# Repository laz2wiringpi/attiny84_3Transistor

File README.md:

# attiny84_3Transistor
attiny84 3 transistor

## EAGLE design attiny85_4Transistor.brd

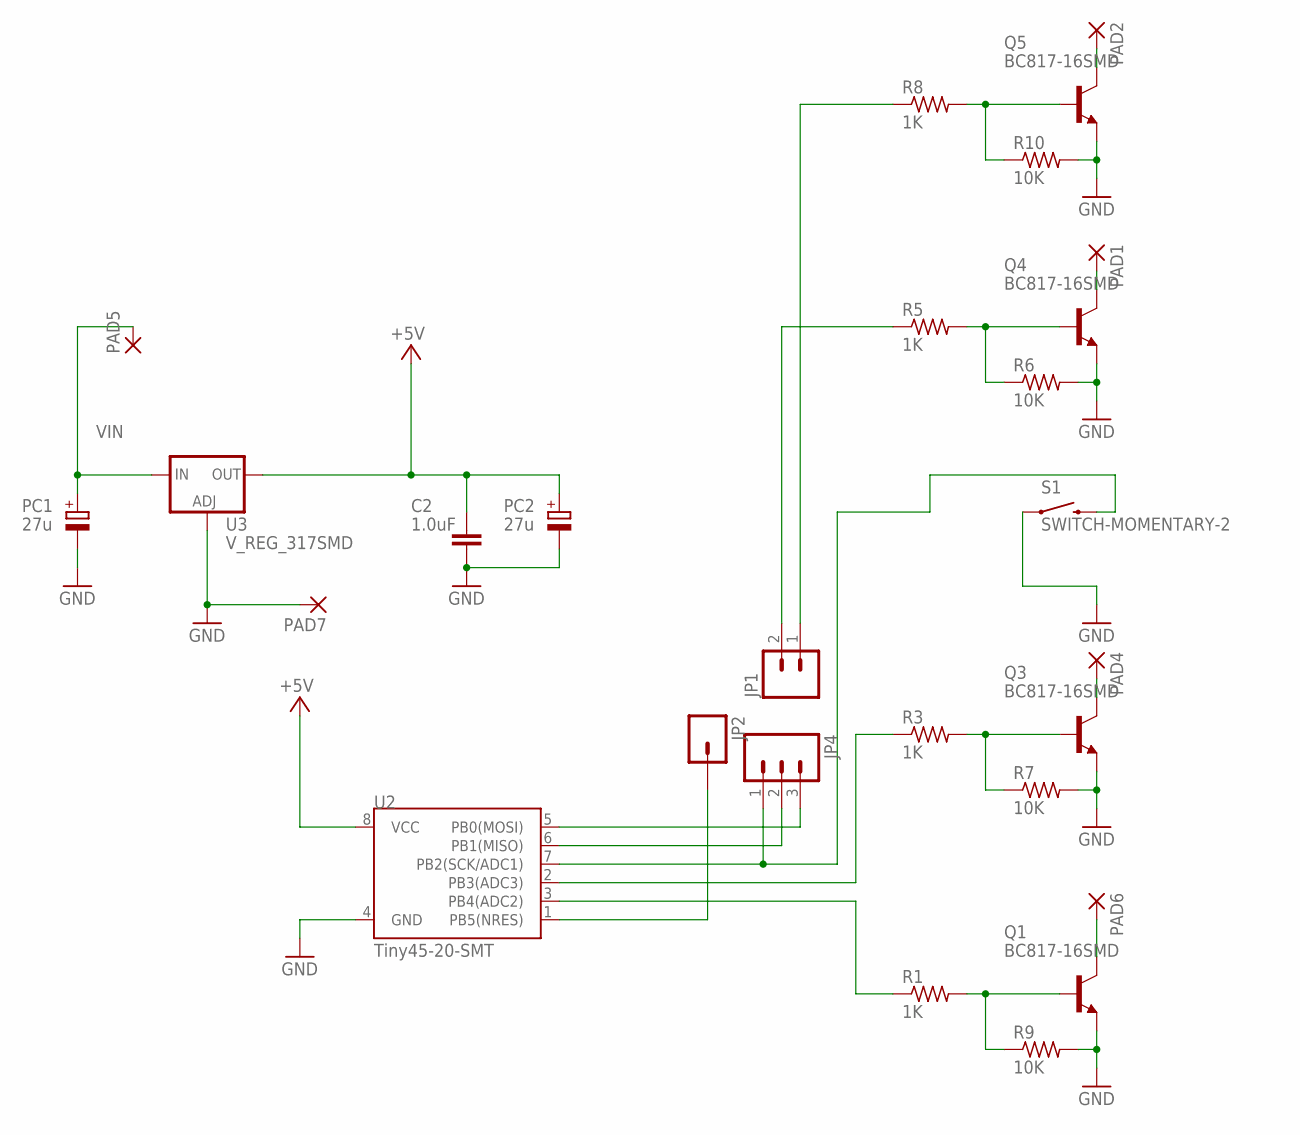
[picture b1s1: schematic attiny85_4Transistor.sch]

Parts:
C2: 1.0uF; 0805
JP1: M021X02_NO_SILK; 1X02_NO_SILK
JP2: M01PTH; 1X01
JP4: M031X03_NO_SILK; 1X03_NO_SILK
PAD1, PAD2, PAD4, PAD5, PAD6, PAD7: 2,15/1,0
PC1, PC2: 27u; E2,5-4R
Q1, Q3, Q4, Q5: BC817-16SMD; SOT23-BEC
R1, R3, R5, R8: 1K; R0805
R6, R7, R9, R10: 10K; M0805
S1: SWITCH-MOMENTARY-2; TACTILE_FSM4JSMATR
U2: Tiny45-20-SMT; SO08-EIAJ
U3: V_REG_317SMD; SOT223

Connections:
+5V: C2.2, PC2.+, U2.8 (VCC), U3.2 (OUT)
GND: C2.1, PAD7.1, PC1.-, PC2.-, Q1.E, Q3.E, Q4.E, Q5.E, R6.2, R7.2, R9.2, R10.2, S1.P$1 (1), S1.P$2 (1), U2.4 (GND), U3.1 (ADJ)
unnamed: Q4.B, R5.2, R6.1
unnamed: JP4.1, S1.P$3 (2), S1.P$4 (2), U2.7 (PB2(SCK/ADC1))
unnamed: Q1.B, R1.2, R9.1
unnamed: Q3.B, R3.2, R7.1
unnamed: PAD1.1, Q4.C
unnamed: PAD6.1, Q1.C
unnamed: JP2.1, U2.1 (PB5(NRES))
unnamed: PAD4.1, Q3.C
unnamed: Q5.B, R8.2, R10.1
unnamed: PAD2.1, Q5.C
PWM2: R3.1, U2.2 (PB3(ADC3))
PWM3: R1.1, U2.3 (PB4(ADC2))
PWM5J: JP1.1, R8.1
PWM5MOSI: JP4.3, U2.5 (PB0(MOSI))
PWM6J: JP1.2, R5.1
PWM6MISO: JP4.2, U2.6 (PB1(MISO))
VIN: PAD5.1, PC1.+, U3.3 (IN)

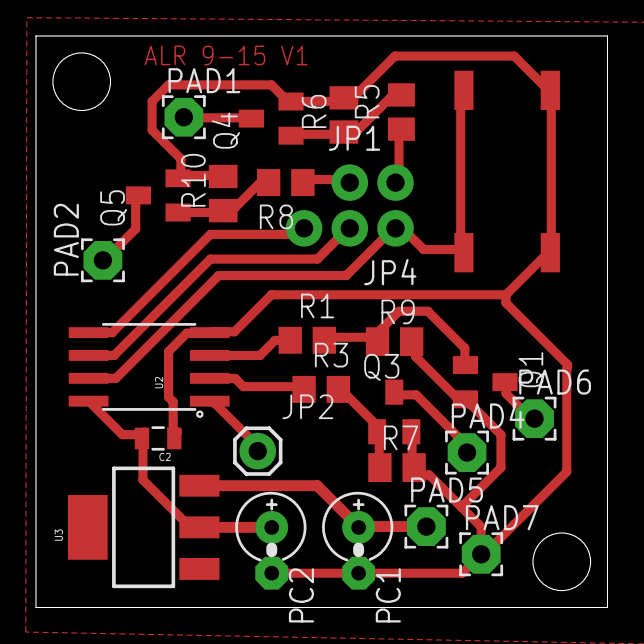
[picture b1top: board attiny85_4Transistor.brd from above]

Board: 2 copper layers, 31.8 x 31.8 mm, 27 parts (0 on the bottom side), 19 nets.

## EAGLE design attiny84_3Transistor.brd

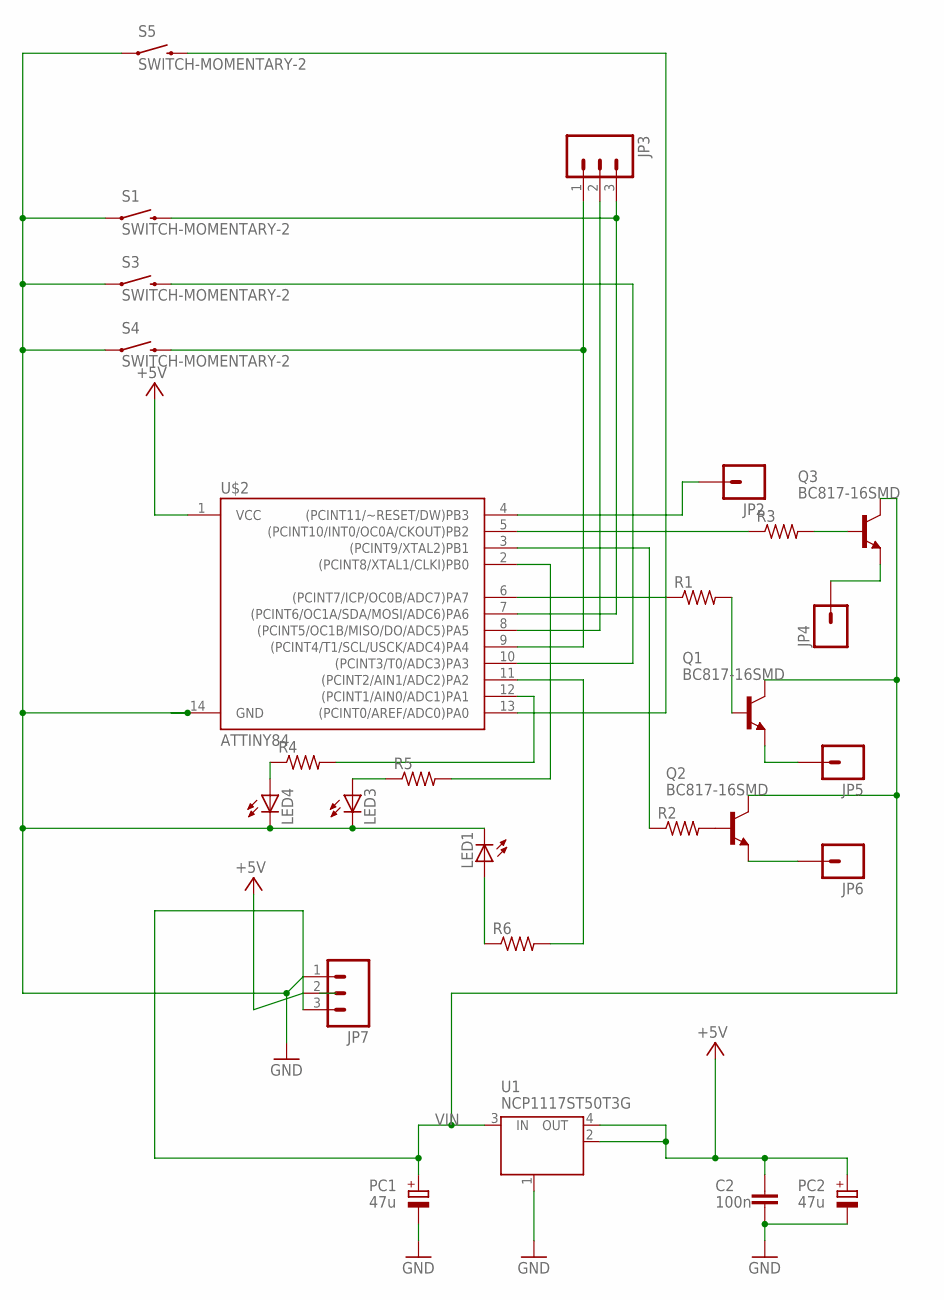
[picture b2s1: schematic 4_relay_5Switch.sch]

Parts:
C2: 100n; C0603-ROUND
JP2, JP4, JP5, JP6: M01NOSILK-KIT; 1X01NS-KIT
JP3, JP7: M031X03_NO_SILK; 1X03_NO_SILK
LED1, LED3, LED4: LEDCHIPLED_0805; CHIPLED_0805
PC1, PC2: 47u; E2,5-4R
Q1, Q2, Q3: BC817-16SMD; SOT23-BEC
R1, R2, R3, R4, R5, R6: R-US_M0805; M0805
S1, S3, S4, S5: SWITCH-MOMENTARY-2; TACTILE_FSM4JSMATR
U1: NCP1117ST50T3G; SOT223
U$2: ATTINY84; SO14

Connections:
+5V: C2.2, JP7.2, PC2.+, U1.2 (OUT), U1.4 (OUT), U$2.1 (VCC)
GND: C2.1, JP7.1, LED1.C, LED3.C, LED4.C, PC1.-, PC2.-, S1.P$1 (1), S1.P$2 (1), S3.P$1 (1), S3.P$2 (1), S4.P$1 (1), S4.P$2 (1), S5.P$1 (1), S5.P$2 (1), U1.1 (GND/ADJ), U$2.14 (GND)
unnamed: JP3.2, U$2.8 ((PCINT5/OC1B/MISO/DO/ADC5)PA5)
unnamed: JP2.1, U$2.4 ((PCINT11/~RESET/DW)PB3)
unnamed: JP3.1, S4.P$3 (2), S4.P$4 (2), U$2.9 ((PCINT4/T1/SCL/USCK/ADC4)PA4)
unnamed: Q1.B, R1.2
unnamed: JP3.3, S1.P$3 (2), S1.P$4 (2), U$2.7 ((PCINT6/OC1A/SDA/MOSI/ADC6)PA6)
unnamed: Q2.B, R2.2
unnamed: Q3.B, R3.2
unnamed: S5.P$3 (2), S5.P$4 (2), U$2.13 ((PCINT0/AREF/ADC0)PA0)
unnamed: R1.1, U$2.6 ((PCINT7/ICP/OC0B/ADC7)PA7)
unnamed: R3.1, U$2.5 ((PCINT10/INT0/OC0A/CKOUT)PB2)
unnamed: R2.1, U$2.3 ((PCINT9/XTAL2)PB1)
unnamed: S3.P$3 (2), S3.P$4 (2), U$2.10 ((PCINT3/T0/ADC3)PA3)
unnamed: R6.2, U$2.11 ((PCINT2/AIN1/ADC2)PA2)
unnamed: JP5.1, Q1.E
unnamed: JP4.1, Q3.E
unnamed: JP6.1, Q2.E
unnamed: R4.2, U$2.12 ((PCINT1/AIN0/ADC1)PA1)
unnamed: R5.2, U$2.2 ((PCINT8/XTAL1/CLKI)PB0)
unnamed: LED4.A, R4.1
unnamed: LED1.A, R6.1
unnamed: LED3.A, R5.1
VIN: JP7.3, PC1.+, Q1.C, Q2.C, Q3.C, U1.3 (IN)

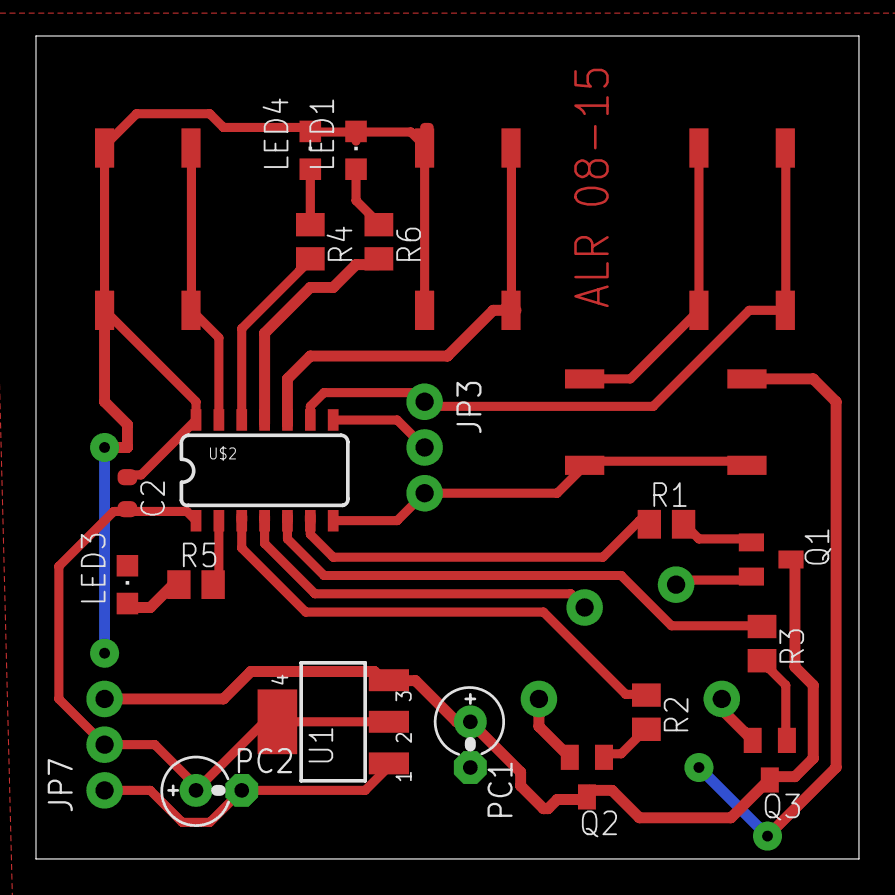
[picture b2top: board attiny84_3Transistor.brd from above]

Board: 2 copper layers, 45.7 x 45.7 mm, 27 parts (0 on the bottom side), 24 nets.

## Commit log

2015-08-27 init
    init
2015-08-27 rename
2015-09-01 85 4 transistor
2015-09-06 add programing
2015-09-06 syncup
2015-09-08 test loop
2015-09-08 ignore git

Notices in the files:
parts and their libraries:
SparkFun-Electromechanical_alr: Licensing: Creative Commons ShareAlike 4.0 International - https://creativecommons.org/licenses/by-sa/4.0
